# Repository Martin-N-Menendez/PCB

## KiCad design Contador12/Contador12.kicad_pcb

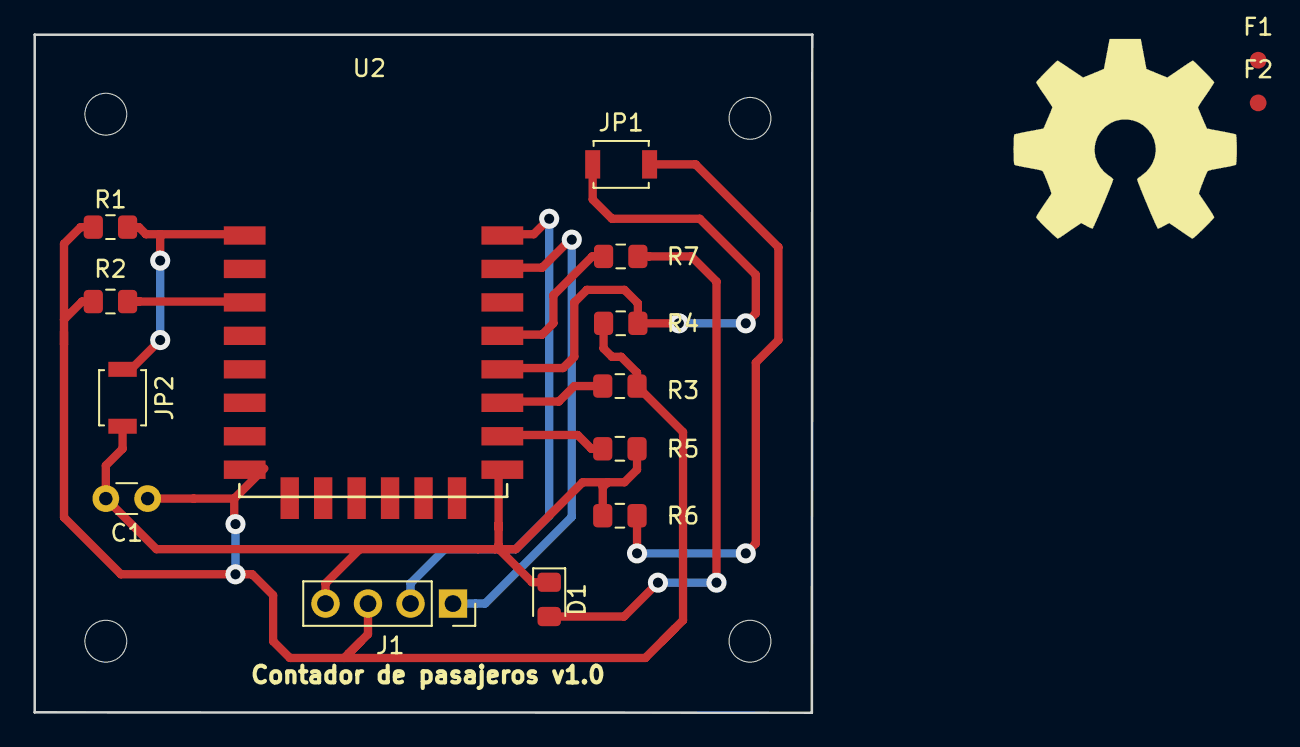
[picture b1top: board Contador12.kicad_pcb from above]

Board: 2 copper layers, 46.5 x 40.5 mm, 20 parts (0 on the bottom side), 12 nets.

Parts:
C1: 100n; C_Disc_D3.0mm_W1.6mm_P2.50mm
D1: LED; LED_0805_2012Metric_Pad1.15x1.40mm_HandSolder
F1, F2: MH2; Fiducial_1mm_Dia_2mm_Outer
J1: Conector_ESP; PinSocket_1x04_P2.54mm_Vertical
JP1, JP2: Jumper; SW_SPST_B3U-1000P
Logo1: Logo_Open_Hardware_Small; OSHW-Symbol_13.4x12mm_SilkScreen
MH1: MH1; MountingHole_2.5mm
MH2: MH2; MountingHole_2.5mm
MH3: MH3; MountingHole_2.5mm
MH4: MH4; MountingHole_2.5mm
R1, R2, R3, R4, R5: 10k; R_0805_2012Metric_Pad1.15x1.40mm_HandSolder
R6, R7: 470; R_0805_2012Metric_Pad1.15x1.40mm_HandSolder
U2: ESP-12E; ESP-12E_SMD

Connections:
+3V3: C1.1, J1.3, R1.1, R2.2, R3.2, R4.1, U2.8
/Program: JP1.1, R4.2, U2.12
/Reset: JP2.1, R1.2, U2.1
/Rx: J1.2, U2.16
/Tx: J1.1, U2.15
GND: C1.2, D1.1, J1.4, JP2.2, R5.2, R6.2, U2.9
unnamed: D1.2, R7.2
unnamed: JP1.2, R6.1
unnamed: R2.1, U2.3
unnamed: R3.1, U2.11
unnamed: R5.1, U2.10
unnamed: R7.1, U2.13

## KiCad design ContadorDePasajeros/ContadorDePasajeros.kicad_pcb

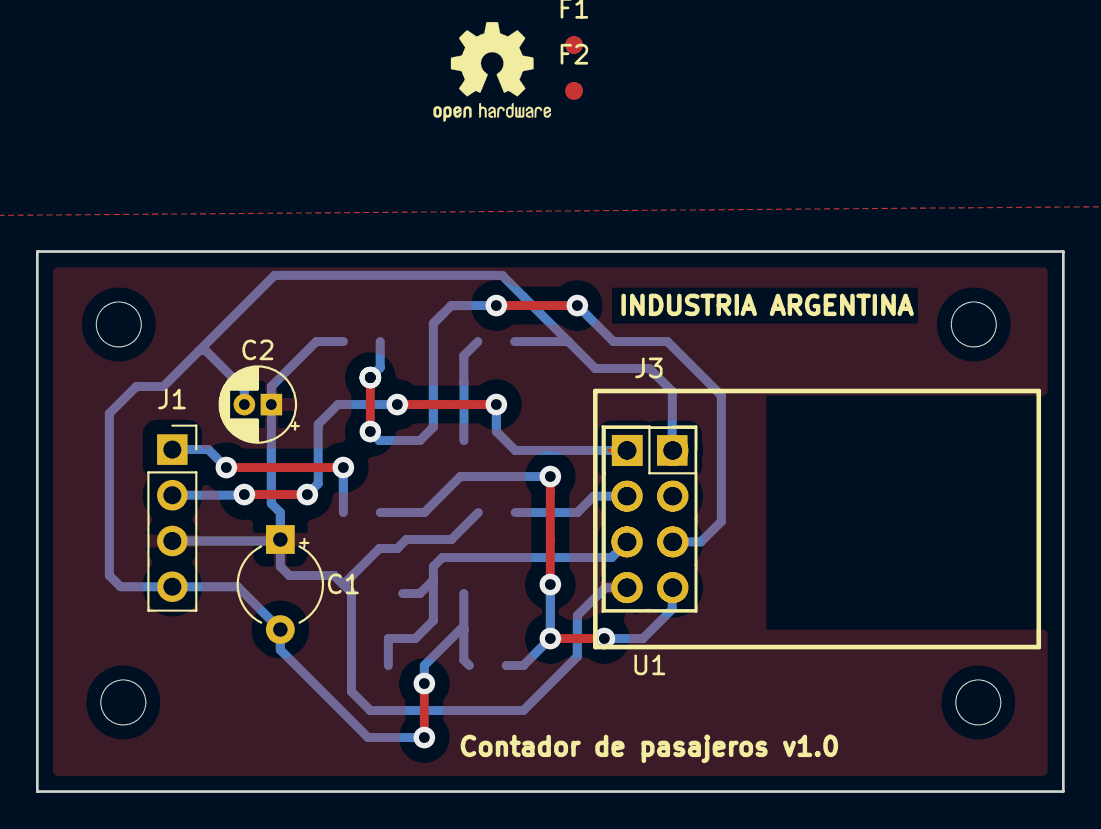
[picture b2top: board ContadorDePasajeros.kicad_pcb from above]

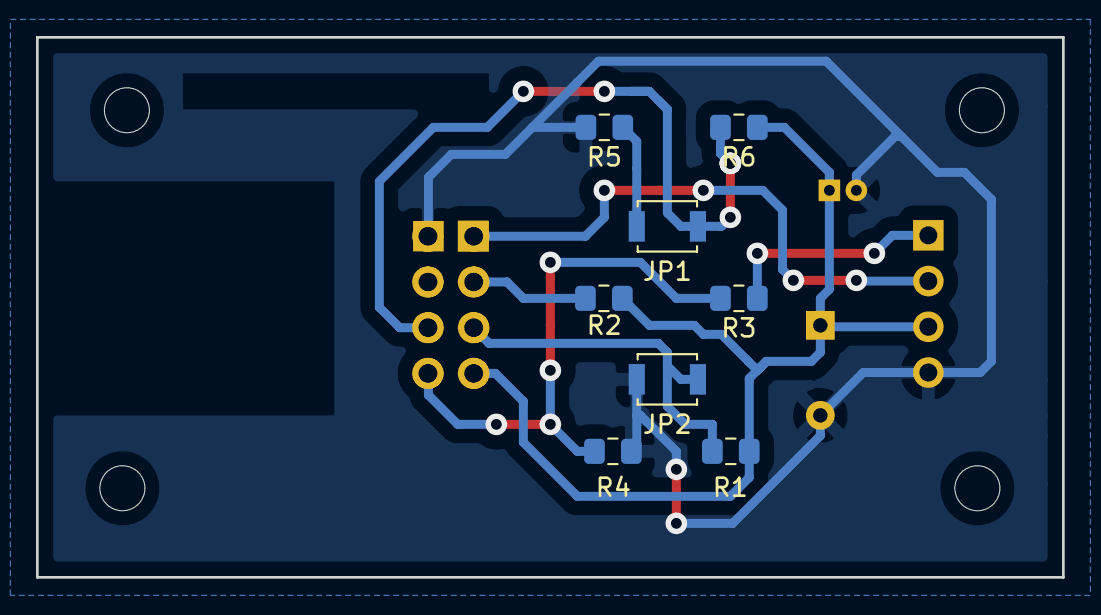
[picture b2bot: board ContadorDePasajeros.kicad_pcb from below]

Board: 2 copper layers, 57.0 x 30.0 mm, 20 parts (8 on the bottom side), 10 nets.

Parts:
C1: 100n; CP_Radial_Tantal_D4.5mm_P5.00mm
C2: 100u; CP_Radial_D4.0mm_P1.50mm
F1, F2: MH4; Fiducial_1mm_Dia_2mm_Outer
J1: Conector_in; PinSocket_1x04_P2.54mm_Vertical
J3: Conector_esp; PinSocket_2x04_P2.54mm_Vertical
JP1, JP2: Jumper; SW_SPST_B3U-1000P
Logo1: Logo_Open_Hardware_Small; OSHW-Logo2_7.3x6mm_SilkScreen
MH1: MH1; MountingHole_2.5mm
MH2: MH2; MountingHole_2.5mm
MH3: MH3; MountingHole_2.5mm
MH4: MH4; MountingHole_2.5mm
R1, R2, R6: 3k3; R_0805_2012Metric_Pad1.15x1.40mm_HandSolder
R3: 1k; R_0805_2012Metric_Pad1.15x1.40mm_HandSolder
R4: 2k; R_0805_2012Metric_Pad1.15x1.40mm_HandSolder
R5: 470; R_0805_2012Metric_Pad1.15x1.40mm_HandSolder
U1: ESP01; ESP-01

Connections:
+3V3: C1.1, C2.1, J1.3, J3.8, R1.2, R2.2, R6.1, U1.7
/Ch: J3.4, R2.1, U1.3
/Gpio0: J3.5, JP1.1, R6.2, U1.6
/Gpio2: J3.3, U1.4
/Rs: J3.6, JP2.1, R1.1, U1.5
/Rx_i: J3.7, R3.2, R4.1, U1.8
GND: C1.2, C2.2, J1.4, J3.1, JP2.2, R4.2, R5.2, U1.2
unnamed: JP1.2, R5.1
Rx: J1.1, R3.1
Tx: J1.2, J3.2, U1.1

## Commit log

2018-11-09 Actualizado
2018-11-10 80% corregido
2018-11-10 Agregado ESP01
2018-11-10 58% completado
2018-11-10 78% completado
2018-11-10 netlist
2018-11-10 57% completado
2018-11-10 80% completado
2018-11-10 88% completado
2018-11-10 Netlist2
2018-11-10 Agregado datasheet
2018-11-10 99% Completado
2018-11-10 82% completado
2018-11-10 96% completado
